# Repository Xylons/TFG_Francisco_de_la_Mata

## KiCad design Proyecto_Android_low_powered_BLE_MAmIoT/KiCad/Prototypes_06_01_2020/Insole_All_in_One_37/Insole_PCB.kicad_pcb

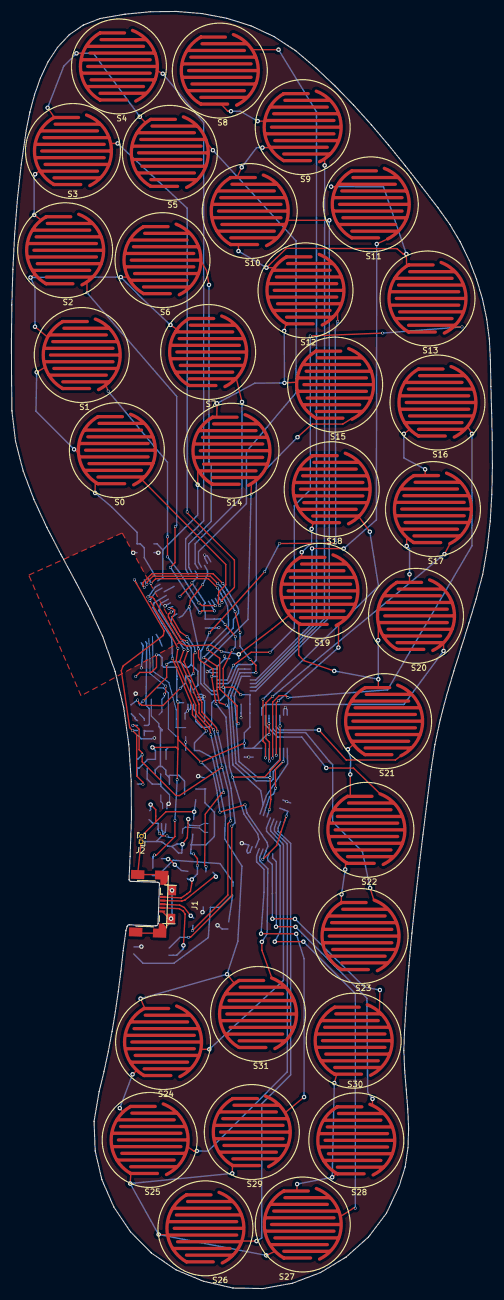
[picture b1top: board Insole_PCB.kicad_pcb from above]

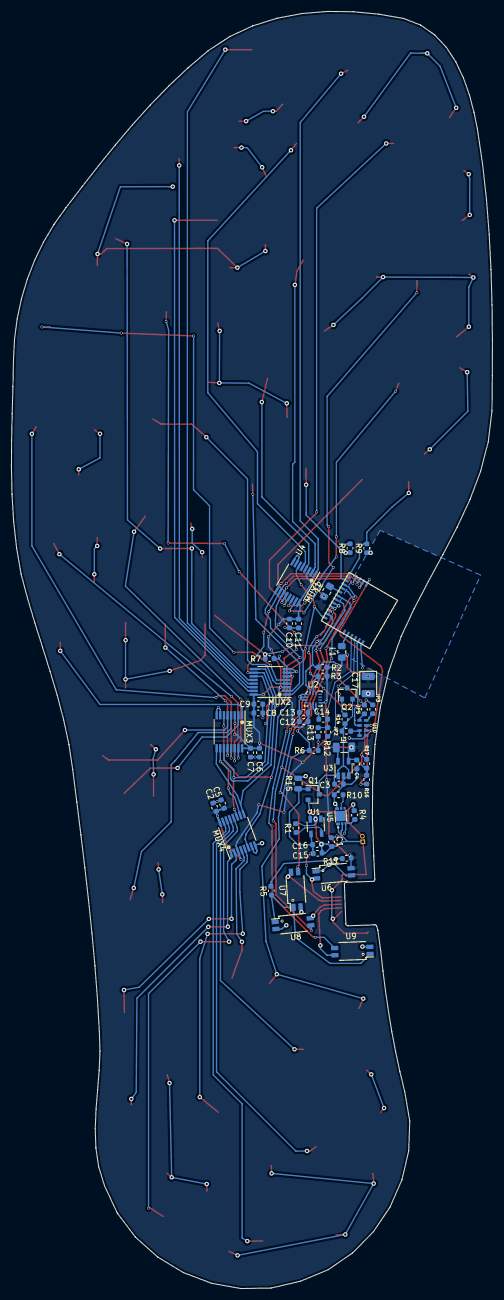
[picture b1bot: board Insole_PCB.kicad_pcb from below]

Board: 2 copper layers, 86.1 x 228.7 mm, 90 parts (56 on the bottom side), 71 nets.

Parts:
C1, C5, C7, C9, C11, C13, C14, C16: 0.1uF; C_0603_1608Metric
C2, C6, C8, C10, C12, C15: 1uF; C_0603_1608Metric
C3: 4.7uF; C_0603_1608Metric
C4: 10uF; C_0603_1608Metric
C17: 100uF; CP_EIA-3528-12_Kemet-T
J1: Conn_Micro_USB; USB_Micro_CustomV2
J2: 3V7_Battery; PinHeader_1x02_P1.00mm_Vertical
JP2, JP3, JP5: Jumper; R_0603_1608Metric
L1, L2: 300ohm 100MHz; L_0805_2012Metric_Pad1.15x1.40mm_HandSolder
L3: 1uH; L_1206_3216Metric
MUX1, MUX2, MUX3, MUX4: CD74HC4051; TSSOP-16_4.4x5mm_P0.65mm
Q1, Q2: Q_PMOS_GSD; SOT-23
R1, R2, R3, R6, R7, R8, R9, R12, R13, R16, R17: 10k; R_0603_1608Metric
R4: 390 ohm; R_0603_1608Metric
R5: 0-1k; R_0603_1608Metric
R10: 2.7k; R_0603_1608Metric
R11: 100-500 ohm; R_0603_1608Metric
R14: 100k; R_0603_1608Metric
R15: 10k; R_0805_2012Metric
S0, S1, S2, S3, S4, S5, S6, S7, S8, S9, S10, S11, S12, S13, S14, S15, S16, S17, S18, S19, S20, S21, S22, S23, S24, S25, S26, S27, S28, S29, S30, S31: FSR; FSR_Circle_7mm
U1: STC4054-4.2; TSOT-23-5
U2: ISM330DLC; Bosch_LGA-14_3x2.5mm_P0.5mm
U3: ADP2108AUJ-3.3; TSOT-23-5
U4: CYBLE-222014-01
U5: AP9211SA-AN-HAC-7; AP9211SAACHAC7
U6, U7, U8, U9: TCMT1100; SOP-4_4.4x2.8mm_P1.27mm
U10: RV8803; RV-8803-C7

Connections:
+3V3: C2.2, C4.1, C5.2, C6.2, C7.2, C8.2, C9.2, C10.2, C11.2, C12.2, C13.2, C17.1, L1.1, L2.1, L3.2, MUX1.3, MUX1.16, MUX2.3, MUX2.16, MUX3.3, MUX3.16, MUX4.3, MUX4.16, R2.1, R3.1, R11.2, R16.1, R17.1, U2.5, U2.8, U3.4, U6.4
+5V: C15.2, C16.2, J1.1, Q1.1, R15.2, U1.4, U6.2
+BATT: J2.2, Q1.2, R4.1, U1.3
-BATT: C1.2, C15.1, C16.1, J1.5, J1.6, J2.1, R1.2, U1.2, U5.1, U5.2
/+3V3_VDD: L2.2, U4.14
/+3V3_VDDR: L1.2, U4.5
/+BATT_CUT: C3.2, JP2.1, Q1.3, Q2.2, R14.1, U3.1, U3.3
/MUX_E: MUX1.6, MUX2.6, MUX3.6, MUX4.6, U4.7
/P0.6_USB: J1.3, U8.4
/P0.7_USB: J1.4, U9.4
/S0: MUX1.11, MUX2.11, MUX3.11, MUX4.11, U4.19
/S1: MUX1.10, MUX2.10, MUX3.10, MUX4.10, U4.20
/S2: MUX1.9, MUX2.9, MUX3.9, MUX4.9, U4.21
/SCL: JP3.2, R3.2, U2.13, U4.10
/SDA: JP5.2, R2.2, U2.14, U4.9
/U1_A0: MUX1.13, S0.2
/U1_A1: MUX1.14, S1.2
/U1_A2: MUX1.15, S2.2
/U1_A3: MUX1.12, S3.2
/U1_A4: MUX1.1, S4.2
/U1_A5: MUX1.5, S5.2
/U1_A6: MUX1.2, S6.2
/U1_A7: MUX1.4, S7.2
/U1_Data: R9.2, S0.1, S1.1, S2.1, S3.1, S4.1, S5.1, S6.1, S7.1, U4.18
/U2_A0: MUX2.13, S8.2
/U2_A1: MUX2.14, S9.2
/U2_A2: MUX2.15, S10.2
/U2_A3: MUX2.12, S11.2
/U2_A4: MUX2.1, S12.2
/U2_A5: MUX2.5, S13.2
/U2_A6: MUX2.2, S14.2
/U2_A7: MUX2.4, S15.2
/U2_Data: R8.2, S8.1, S9.1, S10.1, S11.1, S12.1, S13.1, S14.1, S15.1, U4.17
/U3_A0: MUX3.13, S16.2
/U3_A1: MUX3.14, S17.2
/U3_A2: MUX3.15, S18.2
/U3_A3: MUX3.12, S19.2
/U3_A4: MUX3.1, S20.2
/U3_A5: MUX3.5, S21.2
/U3_A6: MUX3.2, S22.2
/U3_A7: MUX3.4, S23.2
/U3_Data: R7.2, S16.1, S17.1, S18.1, S19.1, S20.1, S21.1, S22.1, S23.1, U4.16
/U4_A0: MUX4.13, S24.2
/U4_A1: MUX4.14, S25.2
/U4_A2: MUX4.15, S26.2
/U4_A3: MUX4.12, S27.2
/U4_A4: MUX4.1, S28.2
/U4_A5: MUX4.5, S29.2
/U4_A6: MUX4.2, S30.2
/U4_A7: MUX4.4, S31.2
/U4_Data: R6.2, S24.1, S25.1, S26.1, S27.1, S28.1, S29.1, S30.1, S31.1, U4.13
/XRES_USB: J1.2, U7.4
Analog_Batt_Lvl: C14.1, R12.2, R13.1, U4.4
Enable_Batt_Lvl: Q2.1, R14.2, U4.3
GND: C2.1, C3.1, C4.2, C5.1, C6.1, C7.1, C8.1, C9.1, C10.1, C11.1, C12.1, C13.1, C14.2, C17.2, MUX1.7, MUX1.8, MUX2.7, MUX2.8, MUX3.7, MUX3.8, MUX4.7, MUX4.8, R6.1, R7.1, R8.1, R9.1, R10.2, R13.2, R15.1, U2.1, U2.2, U2.3, U2.6, U2.7, U3.2, U4.1, U4.11, U5.6, U7.2, U8.2, U9.2, U10.5
unnamed: C1.1, R4.2, U5.3
unnamed: JP2.2, U10.3, U10.4
unnamed: JP3.1, U10.8
unnamed: JP5.1, U10.1
unnamed: L3.1, U3.5
unnamed: Q2.3, R12.1
unnamed: R1.1, U1.5
unnamed: R5.1, U7.1, U8.1, U9.1
unnamed: R5.2, U6.3
unnamed: R10.1, U5.5
unnamed: R11.1, U6.1
P0.6: R17.2, U4.12, U8.3, U10.7
P0.7: U4.8, U9.3
P4.0: R16.2, U4.22, U10.6
P4.1: U4.2, U10.2
XRES: U4.15, U7.3
